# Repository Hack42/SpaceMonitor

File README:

SpaceMonitor controller

Dit project heeft als doel het beter bewaken van de ruimtes in de space. Momenteel wordt de temperatuur gemonitord, en wordt bewaakt of van een aantal ruimtes de ramen gesloten zijn als de SpaceState uit staat.

Het project voorziet in een controller per ruimte, die serieel communiceert met een centraal systeem. Deze controller is gebaseerd op een ATMEGA88 of 168, en is voorzien van 
* 12 I/O poorten (waarvan maximaal 4 als analoge ingang geschakeld kunnen worden)
* 2 open-collector uitgangen, max. 35V 1A
* een Dallas 18B20 voor temperatuurmeting
* optioneel een MAX232 voor de seriele verbinding, wanneer TTL-nivo RS232 niet voldoet

Ramen en deuren kunnen via microswitches verbonden worden met elk een I/O poort. De overige poorten kunnen gebruikt worden voor andere signaalgevers, of om apparatuur aan te sturen. De OC-uitgangen kunnen gebruikt worden om bijvoorbeeld een sirene of een flitslamp te schakelen

https://hack42.nl/wiki/Space_monitoring

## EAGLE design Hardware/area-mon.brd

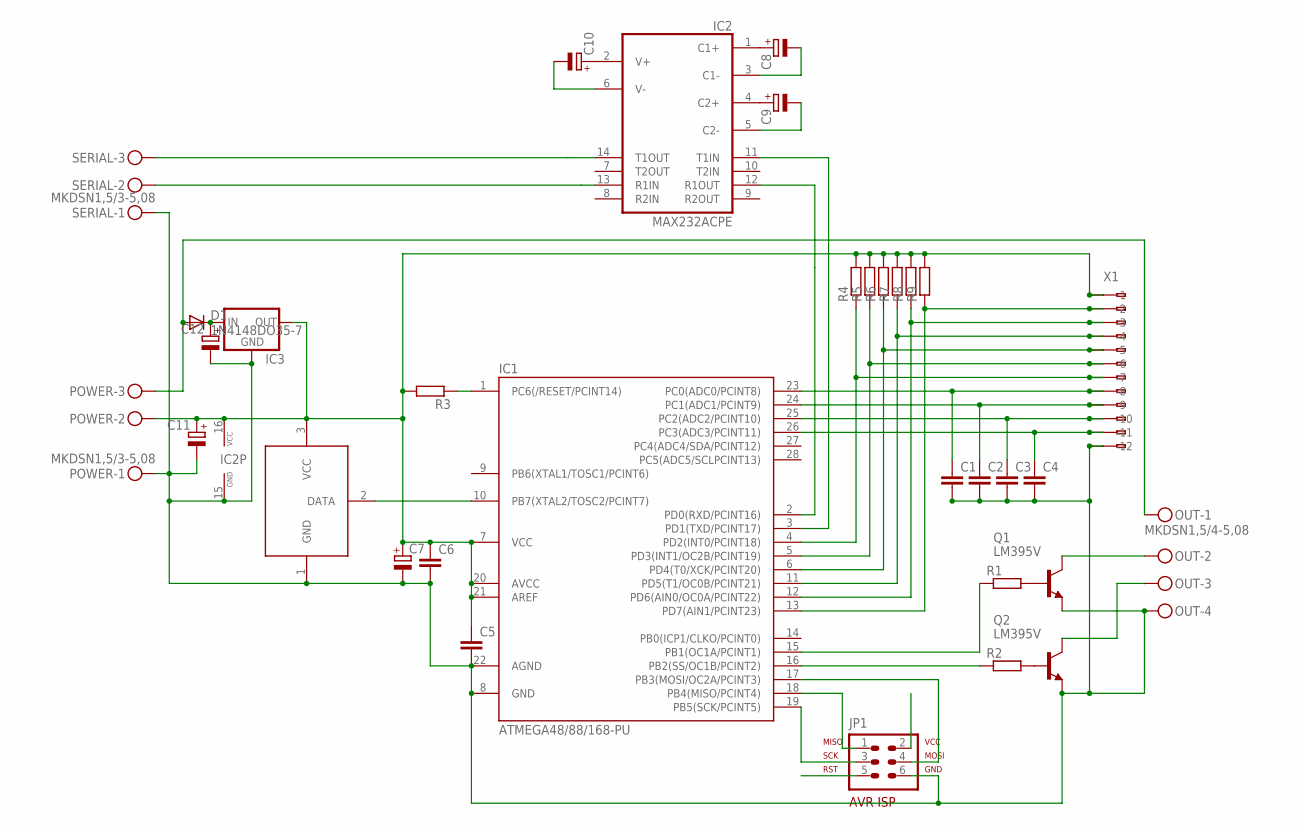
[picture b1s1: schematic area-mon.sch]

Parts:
C1, C2, C3, C4, C5, C6: C-EU050-024X044; C050-024X044
C7: CPOL-EUE5-8.5; E5-8,5
C8, C9, C10, C11, C12: CPOL-EUE2.5-5; E2,5-5
D1: 1N4148DO35-7; DO35-7
IC1: ATMEGA48/88/168-PU; DIL28-3
IC2: MAX232ACPE; DIL16
IC3: 78XXTO92L; TO92L
JP1: AVR-ISP-6VERT; AVR-ISP-6
OUT: MKDSN1,5/4-5,08
POWER: MKDSN1,5/3-5,08
Q1, Q2: LM395V; TO220V
R1, R2, R3, R4, R5, R6, R7, R8, R9: R-EU0207/10; 0207/10
SERIAL: MKDSN1,5/3-5,08
U$4: DS18B20; TO92-
X1: 233-512; MPN 0233-0512

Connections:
1WIRE: IC1.10 (PB7(XTAL2/TOSC2/PCINT7)), U$4.2 (DATA)
GND: C1.2, C2.2, C3.2, C4.2, C5.2, C6.2, C7.-, C11.-, C12.-, IC1.8 (GND), IC1.22 (AGND), IC2.15 (GND), IC3.2 (GND), JP1.6, OUT.4, POWER.1, Q1.C (E), Q2.C (E), SERIAL.1, U$4.1 (GND), X1.A12 (-12), X1.B12 (B-12)
MISO: IC1.18 (PB4(MISO/PCINT4)), JP1.1
MON-A-1: C1.1, IC1.23 (PC0(ADC0/PCINT8)), X1.A8 (-8), X1.B8 (B-8)
MON-A-2: C2.1, IC1.24 (PC1(ADC1/PCINT9)), X1.A9 (-9), X1.B9 (B-9)
MON-A-3: C3.1, IC1.25 (PC2(ADC2/PCINT10)), X1.A10 (-10), X1.B10 (B-10)
MON-A-4: C4.1, IC1.26 (PC3(ADC3/PCINT11)), X1.A11 (-11), X1.B11 (B-11)
MON-D-1: IC1.13 (PD7(AIN1/PCINT23)), R9.1, X1.A2 (-2), X1.B2 (B-2)
MON-D-2: IC1.12 (PD6(AIN0/OC0A/PCINT22)), R8.1, X1.A3 (-3), X1.B3 (B-3)
MON-D-3: IC1.11 (PD5(T1/OC0B/PCINT21)), R7.1, X1.A4 (-4), X1.B4 (B-4)
MON-D-4: IC1.6 (PD4(T0/XCK/PCINT20)), R6.1, X1.A5 (-5), X1.B5 (B-5)
MON-D-5: IC1.5 (PD3(INT1/OC2B/PCINT19)), R5.1, X1.A6 (-6), X1.B6 (B-6)
MON-D-6: IC1.4 (PD2(INT0/PCINT18)), R4.1, X1.A7 (-7), X1.B7 (B-7)
MOSI: IC1.17 (PB3(MOSI/OC2A/PCINT3)), JP1.4
unnamed: Q1.B, R1.2
unnamed: Q2.B, R2.2
unnamed: D1.A, OUT.1, POWER.3
unnamed: OUT.2, Q1.E (C)
unnamed: OUT.3, Q2.E (C)
unnamed: C8.+, IC2.1 (C1+)
unnamed: C9.+, IC2.4 (C2+)
unnamed: C9.-, IC2.5 (C2-)
unnamed: C8.-, IC2.3 (C1-)
unnamed: C10.+, IC2.2 (V+)
unnamed: C10.-, IC2.6 (V-)
unnamed: C12.+, D1.C, IC3.1 (IN)
OUT-CH-1: IC1.15 (PB1(OC1A/PCINT1)), R1.1
OUT-CH-2: IC1.16 (PB2(SS/OC1B/PCINT2)), R2.1
RST: IC1.1 (PC6(/RESET/PCINT14)), JP1.5, R3.1
RX-232: IC2.13 (R1IN), SERIAL.2
RXD: IC1.2 (PD0(RXD/PCINT16)), IC2.12 (R1OUT)
SCK: IC1.19 (PB5(SCK/PCINT5)), JP1.3
TX-232: IC2.14 (T1OUT), SERIAL.3
TXD: IC1.3 (PD1(TXD/PCINT17)), IC2.11 (T1IN)
VCC: C5.1, C6.1, C7.+, C11.+, IC1.7 (VCC), IC1.20 (AVCC), IC1.21 (AREF), IC2.16 (VCC), IC3.3 (OUT), JP1.2, POWER.2, R3.2, R4.2, R5.2, R6.2, R7.2, R8.2, R9.2, U$4.3 (VCC), X1.A1 (-1), X1.B1 (B-1)

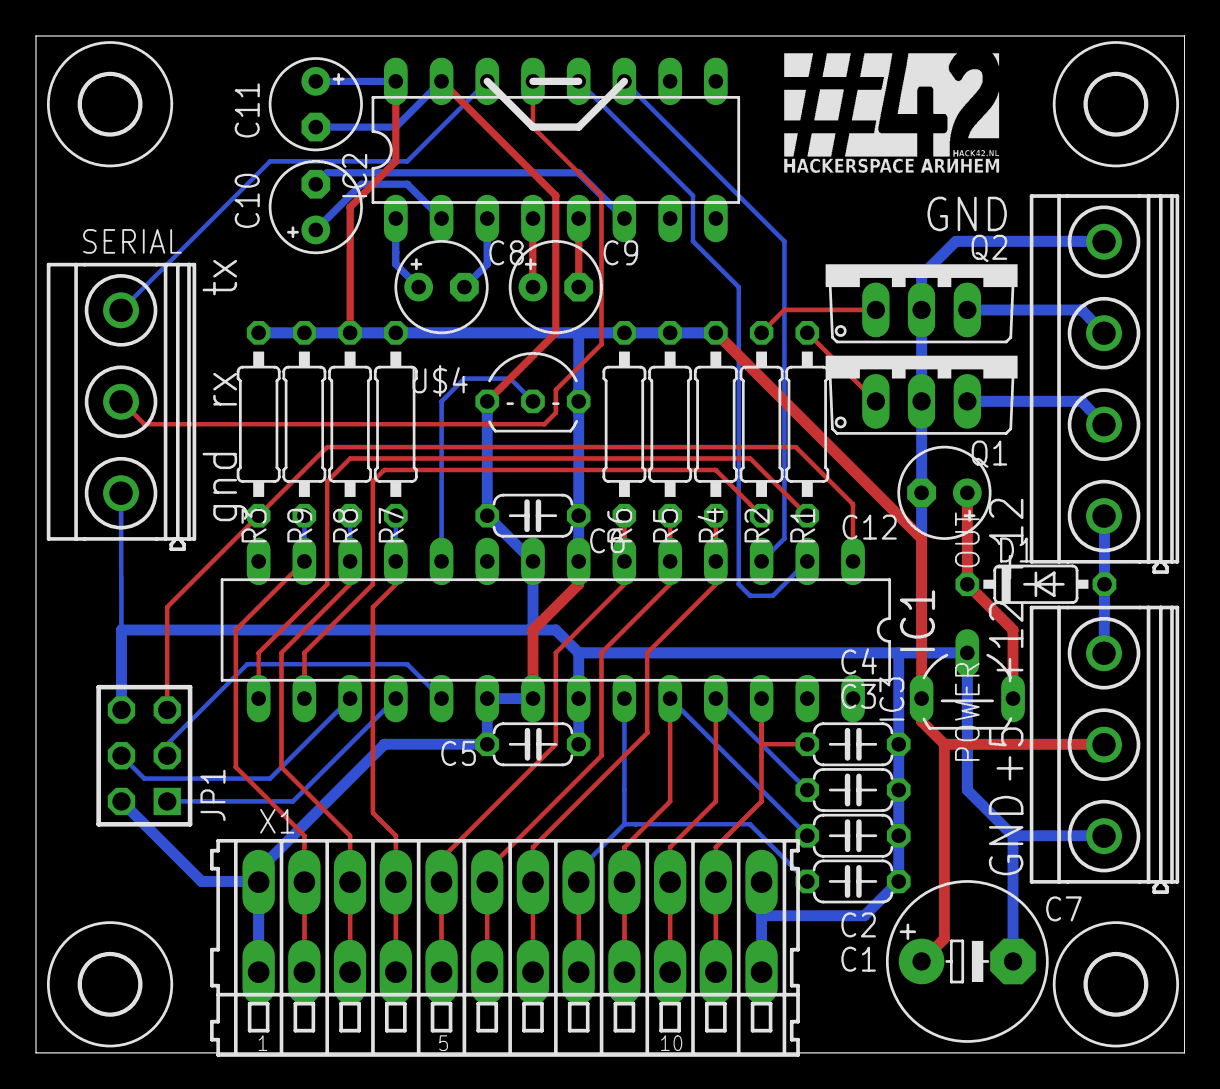
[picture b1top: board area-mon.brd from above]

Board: 2 copper layers, 63.8 x 56.5 mm, 38 parts (0 on the bottom side), 35 nets.

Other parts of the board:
U$1, U$2, U$3, U$5: 3,2
U$6: LOGO_HACK42-12X7

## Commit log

2013-10-03 Initial checkin
2013-10-03 Added README
2014-01-09 Initial commit of the Bootloader software
